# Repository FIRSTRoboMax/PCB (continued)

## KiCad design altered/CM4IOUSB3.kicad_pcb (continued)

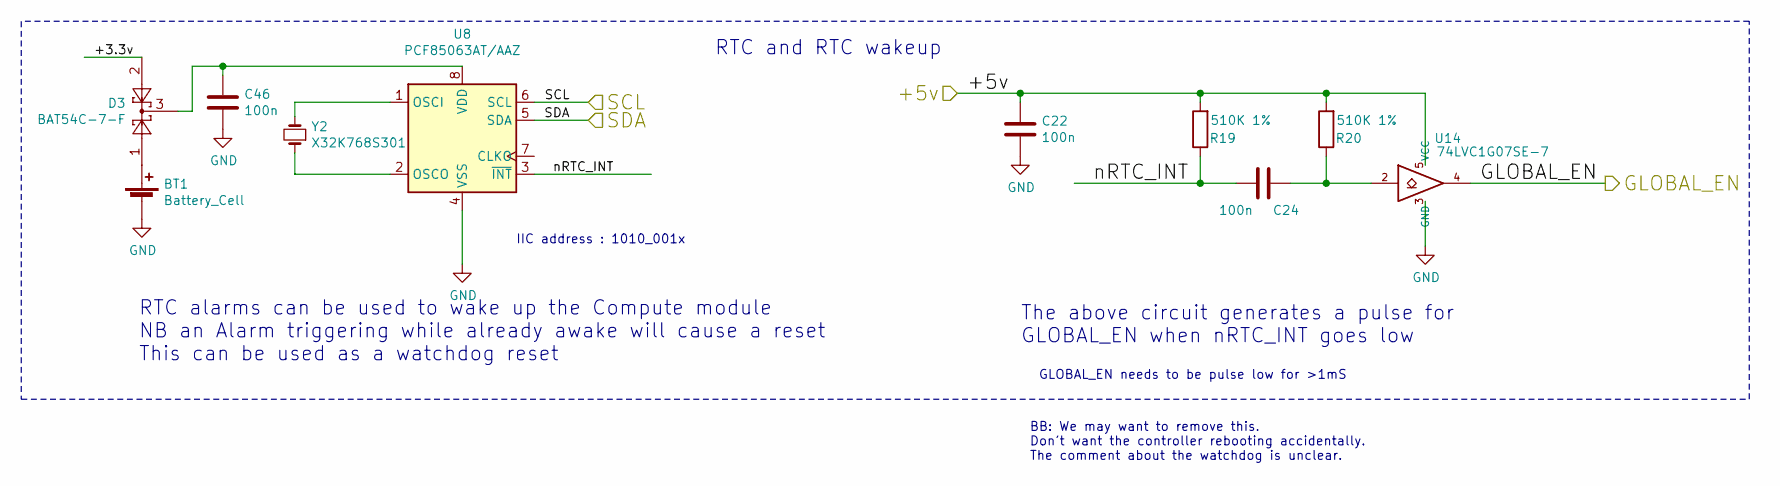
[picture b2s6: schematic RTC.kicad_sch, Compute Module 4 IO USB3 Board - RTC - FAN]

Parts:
BT1: Battery_Cell; BatteryHolder_Keystone_3034_1x20mm; Part Description Battery Retainer Coin, 20.0mm 1 Cell SM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
C22, C24, C46: 100n; C_0402_1005Metric; Part Description 0.1uF 10% 16V Ceramic Capacitor X7R 040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
D3: BAT54C-7-F; SOT-23; Part Description Diode Array 1 Pair Common Cathode Schot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
R19, R20: 510K 1%; R_0402_1005Metric; Part Description Resistor 510K M1005 1% 63mW
U8: PCF85063AT/AAZ; SOIC-8_3.9x4.9mm_P1.27mm; Part Description Real Time Clock (RTC) IC Clock/Calendar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
U14: 74LVC1G07SE-7; SOT-353_SC-70-5; Part Description Buffer, Non-Inverting 1 Element 1 Bit p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
Y2: X32K768S301; Crystal_SMD_3215-2Pin_3.2x1.5mm; Part Description Crystal 32.768KHz 7pF 20pmm

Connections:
/+5v: C22.1, R19.2, R20.2, U14.5 (VCC); also elsewhere on the board
/CM4_GPIO ( Ethernet, GPIO, SDCARD)/GLOBAL_EN: U14.4; also elsewhere on the board
/RTC , Wakeup, FAN/+3.3v: D3.2
/RTC , Wakeup, FAN/SCL: U8.6 (SCL); also elsewhere on the board
/RTC , Wakeup, FAN/SDA: U8.5 (SDA); also elsewhere on the board
/RTC , Wakeup, FAN/nRTC_INT: C24.2, R19.1, U8.3 (~INT)
GND: BT1.2 (-), C22.2, C46.2, U8.4 (VSS), U14.3 (GND); also elsewhere on the board
unnamed: BT1.1 (+), D3.1
unnamed: C24.1, R20.1, U14.2
unnamed: U8.1 (OSCI), Y2.2
unnamed: U8.2 (OSCO), Y2.1
unnamed: C46.1, D3.3, U8.8 (VDD)

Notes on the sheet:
BB: We may want to remove this. Don't want the controller rebooting accidentally. The comment about the watchdog is unclear.
GLOBAL_EN needs to be pulse low for >1mS
RTC and RTC wakeup
The above circuit generates a pulse for GLOBAL_EN when nRTC_INT goes low
IIC address : 1010_001x
RTC alarms can be used to wake up the Compute module NB an Alarm triggering while already awake will cause a reset This can be used as a watchdog reset

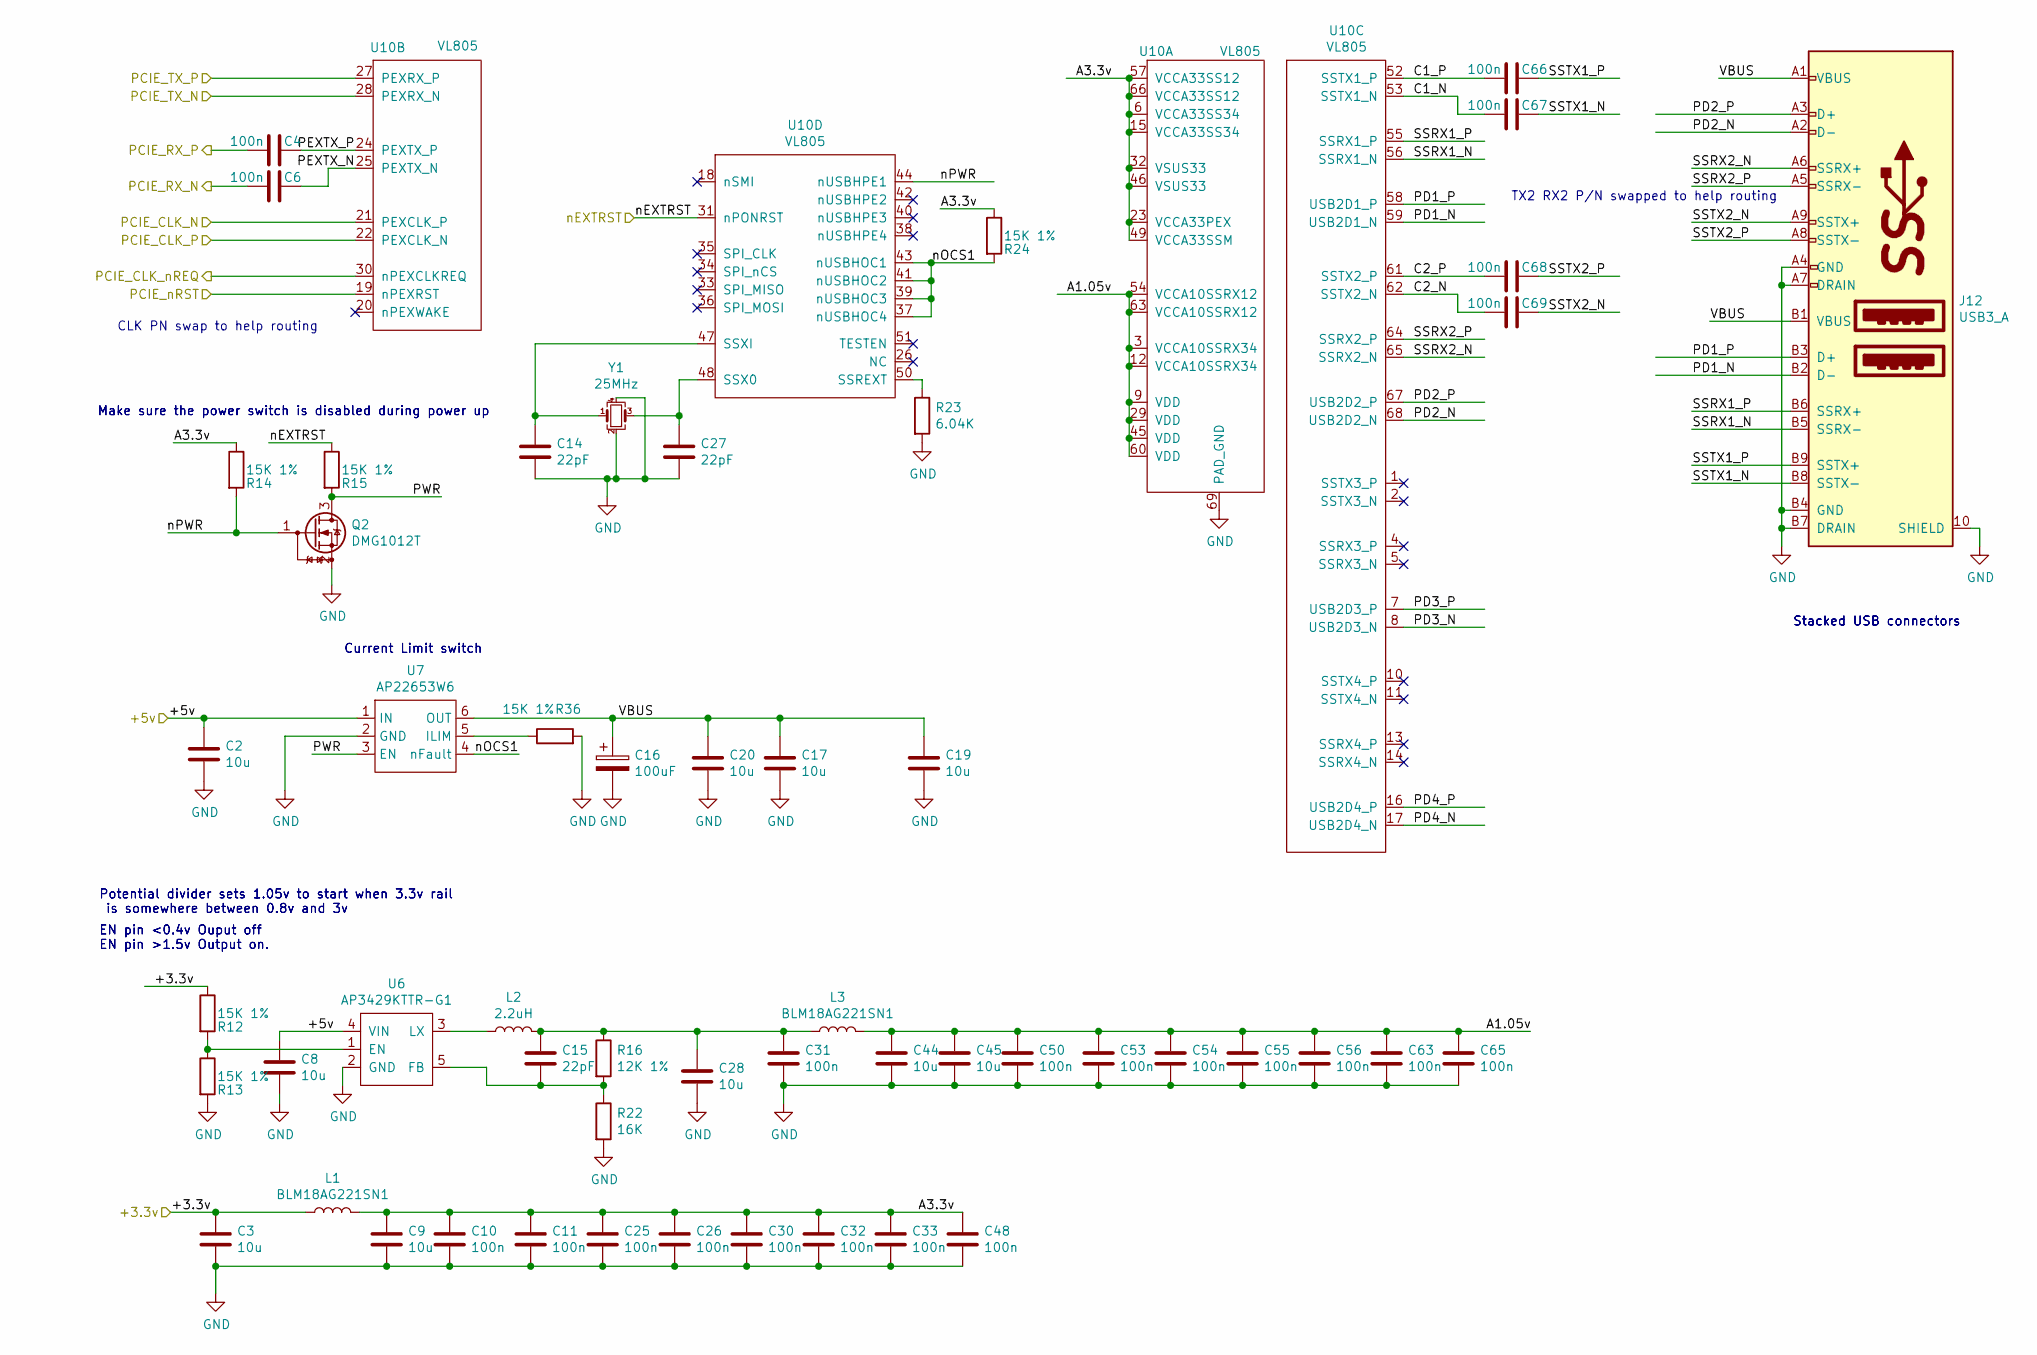
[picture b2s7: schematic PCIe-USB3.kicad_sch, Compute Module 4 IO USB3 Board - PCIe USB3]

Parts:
C2, C3, C8, C9, C17, C19, C20, C28, C44, C45: 10u; C_0805_2012Metric; Part Description 10uF 10% 10V Ceramic Capacitor X7R 0805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
C4, C6, C10, C11, C25, C26, C30, C31, C32, C33, C48, C50, C53, C54, C55, C56, C63, C65, C66, C67, C68, C69: 100n; C_0402_1005Metric; Part Description 0.1uF 10% 16V Ceramic Capacitor X7R 040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
C14, C15, C27: 22pF; C_0402_1005Metric
C16: 100uF; CP_EIA-7343-31_Kemet-D; Part Description Capacitor, SP-Cap, 100u, 6.3V, 15mR ESR
J12: USB3_A; MTCONN_UBAF30-D2011
L1, L3: BLM18AG221SN1; L_0603_1608Metric; Part Description Ferrite Bead, M1608, 220R@100MHz, 100mR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
L2: 2.2uH; L_1008_2520Metric; Part Description Inductor, SMT, 2520, 2u2, IRMS=2.3A, IS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
Q2: DMG1012T; SOT-523
R12, R13, R14, R15, R24, R36: 15K 1%; R_0402_1005Metric; Part Description Resistor 15K M1005 1% 63mW
R16: 12K 1%; R_0402_1005Metric; Part Description Resistor 12K M1005 1% 63mW
R22: 16K; R_0402_1005Metric; Part Description Resistor 16K M1005 1% 63mW
R23: 6.04K; R_0402_1005Metric; Part Description Resistor 6.04K M1005 1% 63mW
U6: AP3429KTTR-G1; TSOT-23-5
U7: AP22653W6; SOT-23-6; Part Description Power Switch/Driver 1:1 P-Channel 2.1A 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
U10: VL805; QFN-68-1EP_8x8mm_P0.4mm_EP5.2x5.2mm_ThermalVias
Y1: 25MHz; Crystal_SMD_SeikoEpson_FA238-4Pin_3.2x2.5mm; Part Description Crystal 25MHz 3.2x2.5mm 30ppm 50R 14pF 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

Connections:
/+3.3v: C3.1, L1.1, R12.1; also elsewhere on the board
/+5v: C2.1, C8.1, U6.4 (VIN), U7.1 (IN); also elsewhere on the board
/CM4_HighSpeed/PCIE_CLK_N: U10.21 (PEXCLK_P); also elsewhere on the board
/CM4_HighSpeed/PCIE_CLK_P: U10.22 (PEXCLK_N); also elsewhere on the board
/CM4_HighSpeed/PCIE_CLK_nREQ: U10.30 (nPEXCLKREQ); also elsewhere on the board
/CM4_HighSpeed/PCIE_RX_N: C6.2; also elsewhere on the board
/CM4_HighSpeed/PCIE_RX_P: C4.2; also elsewhere on the board
/CM4_HighSpeed/PCIE_TX_N: U10.28 (PEXRX_N); also elsewhere on the board
/CM4_HighSpeed/PCIE_TX_P: U10.27 (PEXRX_P); also elsewhere on the board
/CM4_HighSpeed/PCIE_nRST: U10.19 (nPEXRST); also elsewhere on the board
/nEXTRST: R15.1, U10.31 (nPONRST); also elsewhere on the board
/xHCI-USB3/A1.05v: C44.1, C45.1, C50.1, C53.1, C54.1, C55.1, C56.1, C63.1, C65.1, L3.2, U10.3 (VCCA10SSRX34), U10.9 (VDD), U10.12 (VCCA10SSRX34), U10.29 (VDD), U10.45 (VDD), U10.54 (VCCA10SSRX12), U10.60 (VDD), U10.63 (VCCA10SSRX12)
/xHCI-USB3/A3.3v: C9.1, C10.1, C11.1, C25.1, C26.1, C30.1, C32.1, C33.1, C48.1, L1.2, R14.1, R24.1, U10.6 (VCCA33SS34), U10.15 (VCCA33SS34), U10.23 (VCCA33PEX), U10.32 (VSUS33), U10.46 (VSUS33), U10.49 (VCCA33SSM), U10.57 (VCCA33SS12), U10.66 (VCCA33SS12)
/xHCI-USB3/C1_N: C67.2, U10.53 (SSTX1_N)
/xHCI-USB3/C1_P: C66.2, U10.52 (SSTX1_P)
/xHCI-USB3/C2_N: C69.2, U10.62 (SSTX2_N)
/xHCI-USB3/C2_P: C68.2, U10.61 (SSTX2_P)
/xHCI-USB3/PD1_N: J12.B2 (D-), U10.59 (USB2D1_N)
/xHCI-USB3/PD1_P: J12.B3 (D+), U10.58 (USB2D1_P)
/xHCI-USB3/PD2_N: J12.A2 (D-), U10.68 (USB2D2_N)
/xHCI-USB3/PD2_P: J12.A3 (D+), U10.67 (USB2D2_P)
/xHCI-USB3/PD3_N: U10.8 (USB2D3_N)
/xHCI-USB3/PD3_P: U10.7 (USB2D3_P)
/xHCI-USB3/PD4_N: U10.17 (USB2D4_N)
/xHCI-USB3/PD4_P: U10.16 (USB2D4_P)
/xHCI-USB3/PEXTX_N: C6.1, U10.25 (PEXTX_N)
/xHCI-USB3/PEXTX_P: C4.1, U10.24 (PEXTX_P)
/xHCI-USB3/PWR: Q2.3 (D), R15.2, U7.3 (EN)
/xHCI-USB3/SSRX1_N: J12.B5 (SSRX-), U10.56 (SSRX1_N)
/xHCI-USB3/SSRX1_P: J12.B6 (SSRX+), U10.55 (SSRX1_P)
/xHCI-USB3/SSRX2_N: J12.A6 (SSRX+), U10.65 (SSRX2_N)
/xHCI-USB3/SSRX2_P: J12.A5 (SSRX-), U10.64 (SSRX2_P)
/xHCI-USB3/SSTX1_N: C67.1, J12.B8 (SSTX-)
/xHCI-USB3/SSTX1_P: C66.1, J12.B9 (SSTX+)
/xHCI-USB3/SSTX2_N: C69.1, J12.A9 (SSTX+)
/xHCI-USB3/SSTX2_P: C68.1, J12.A8 (SSTX-)
/xHCI-USB3/VBUS: C16.1, C17.1, C19.1, C20.1, J12.A1 (VBUS), J12.B1 (VBUS), U7.6 (OUT)
/xHCI-USB3/nOCS1: R24.2, U7.4 (nFault), U10.37 (nUSBHOC4), U10.39 (nUSBHOC3), U10.41 (nUSBHOC2), U10.43 (nUSBHOC1)
/xHCI-USB3/nPWR: Q2.1 (G), R14.2, U10.44 (nUSBHPE1)
GND: C2.2, C3.2, C8.2, C9.2, C10.2, C11.2, C14.2, C16.2, C17.2, C19.2, C20.2, C25.2, C26.2, C27.2, C28.2, C30.2, C31.2, C32.2, C33.2, C44.2, C45.2, C48.2, C50.2, C53.2, C54.2, C55.2, C56.2, C63.2, C65.2, J12.10 (SHIELD), J12.A4 (GND), J12.A7 (DRAIN), J12.B4 (GND), J12.B7 (DRAIN), Q2.2 (S), R13.2, R22.2, R23.2, R36.2, U6.2 (GND), U7.2 (GND), U10.69 (PAD_GND), Y1.2, Y1.4; also elsewhere on the board
unnamed: C15.1, C28.1, C31.1, L2.2, L3.1, R16.1
unnamed: R12.2, R13.1, U6.1 (EN)
unnamed: C15.2, R16.2, R22.1, U6.5 (FB)
unnamed: L2.1, U6.3 (LX)
unnamed: R36.1, U7.5 (ILIM)
unnamed: R23.1, U10.50 (SSREXT)
unnamed: C27.1, U10.48 (SSX0), Y1.3
unnamed: C14.1, U10.47 (SSXI), Y1.1

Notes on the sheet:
Potential divider sets 1.05v to start when 3.3v rail is somewhere between 0.8v and 3v
Current Limit switch
CLK PN swap to help routing
TX2 RX2 P/N swapped to help routing
Stacked USB connectors
Make sure the power switch is disabled during power up
EN pin <0.4v Ouput off EN pin >1.5v Output on.

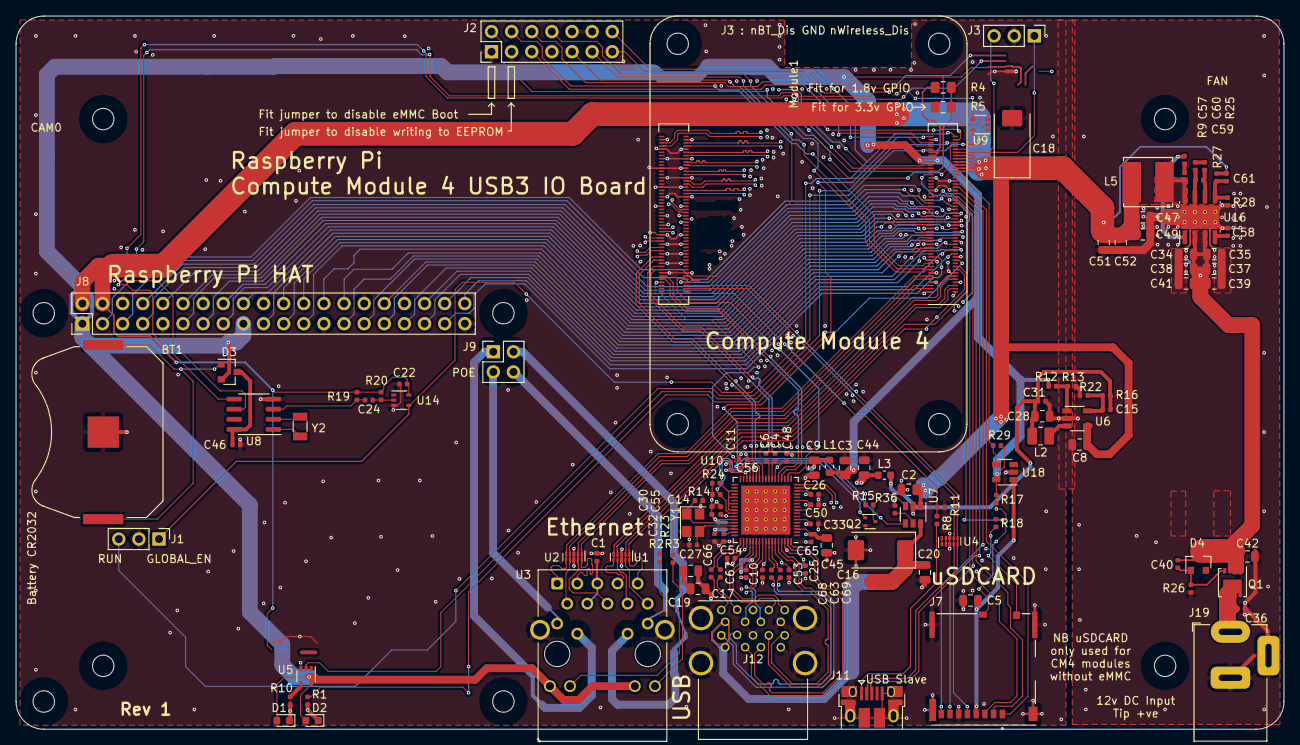
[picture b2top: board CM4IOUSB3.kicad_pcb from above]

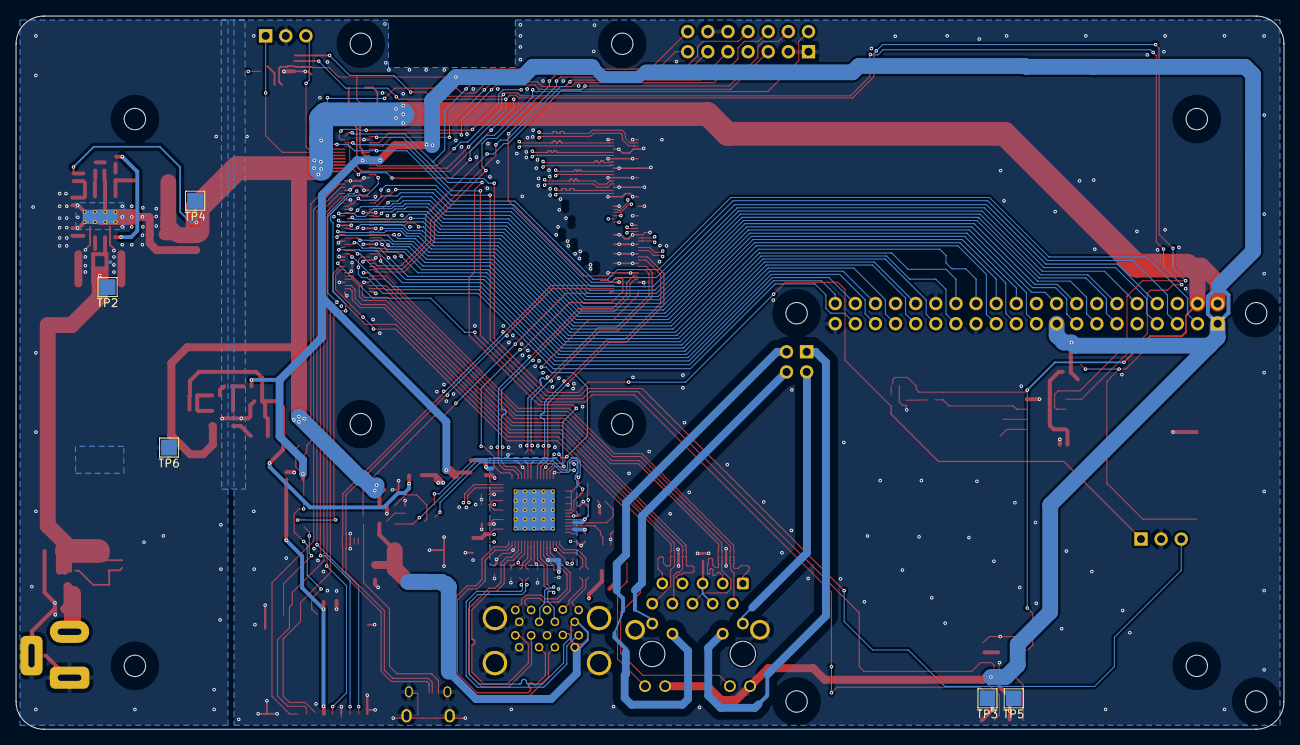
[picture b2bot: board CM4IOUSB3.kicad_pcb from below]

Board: 4 copper layers, 160.0 x 90.0 mm, 136 parts (5 on the bottom side), 142 nets.

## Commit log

2023-12-17 RPi Ref Design Downloaded 17 Dec 2023
    https://datasheets.raspberrypi.com/cm4io/CM4IOUSB3-KiCAD.zip:
2023-12-17 Add gitignore
    https://github.com/github/gitignore/blob/main/KiCad.gitignore
2023-12-17 Add 3d models per readme.txt
2023-12-17 Removing unneeded items
2023-12-17 Remove old gerbers
2023-12-17 Move to subdirectory
2023-12-17 Starting with a rough PCB adding big components
2023-12-17 Add footprints and symbols for components we plan to use
2023-12-17 Break libs by MFG
2023-12-17 Playing with weidmuller
